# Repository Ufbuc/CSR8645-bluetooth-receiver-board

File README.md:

# CSR8645-bluetooth-receiver-board
Breakout board for F-3188 V2.0 bluetooth board with single ended output signal and onboard power supply.

This is a simple circuit board (43mm x 64mm) to make use of the features of the very common *F-3188 V2.0* which is based on the Qualcomm *CSR8645*. Simply connect power (5V via USB Type B or up to 15V via pin header) and 3.5mm phone connector to get an audio signal in aptX quality.

Pin headers can be used to connect status LEDs and control buttons. Many features can be customized by connecting a supported programmer.
A *MAX97220* board converts the differential ended signal from the *CSR8645* to a single ended signal. The onboard power supply uses a *LD1117 SC-R* to provide a stable input voltage (3.5-3.6V) for both mounted PCBs.

The output level is high enough to drive a dedicated amplifier. If the board is used to directly drive headphones it may be better to skip the onboard power supply and use 5V input voltage as input voltage for the *MAX97220*.

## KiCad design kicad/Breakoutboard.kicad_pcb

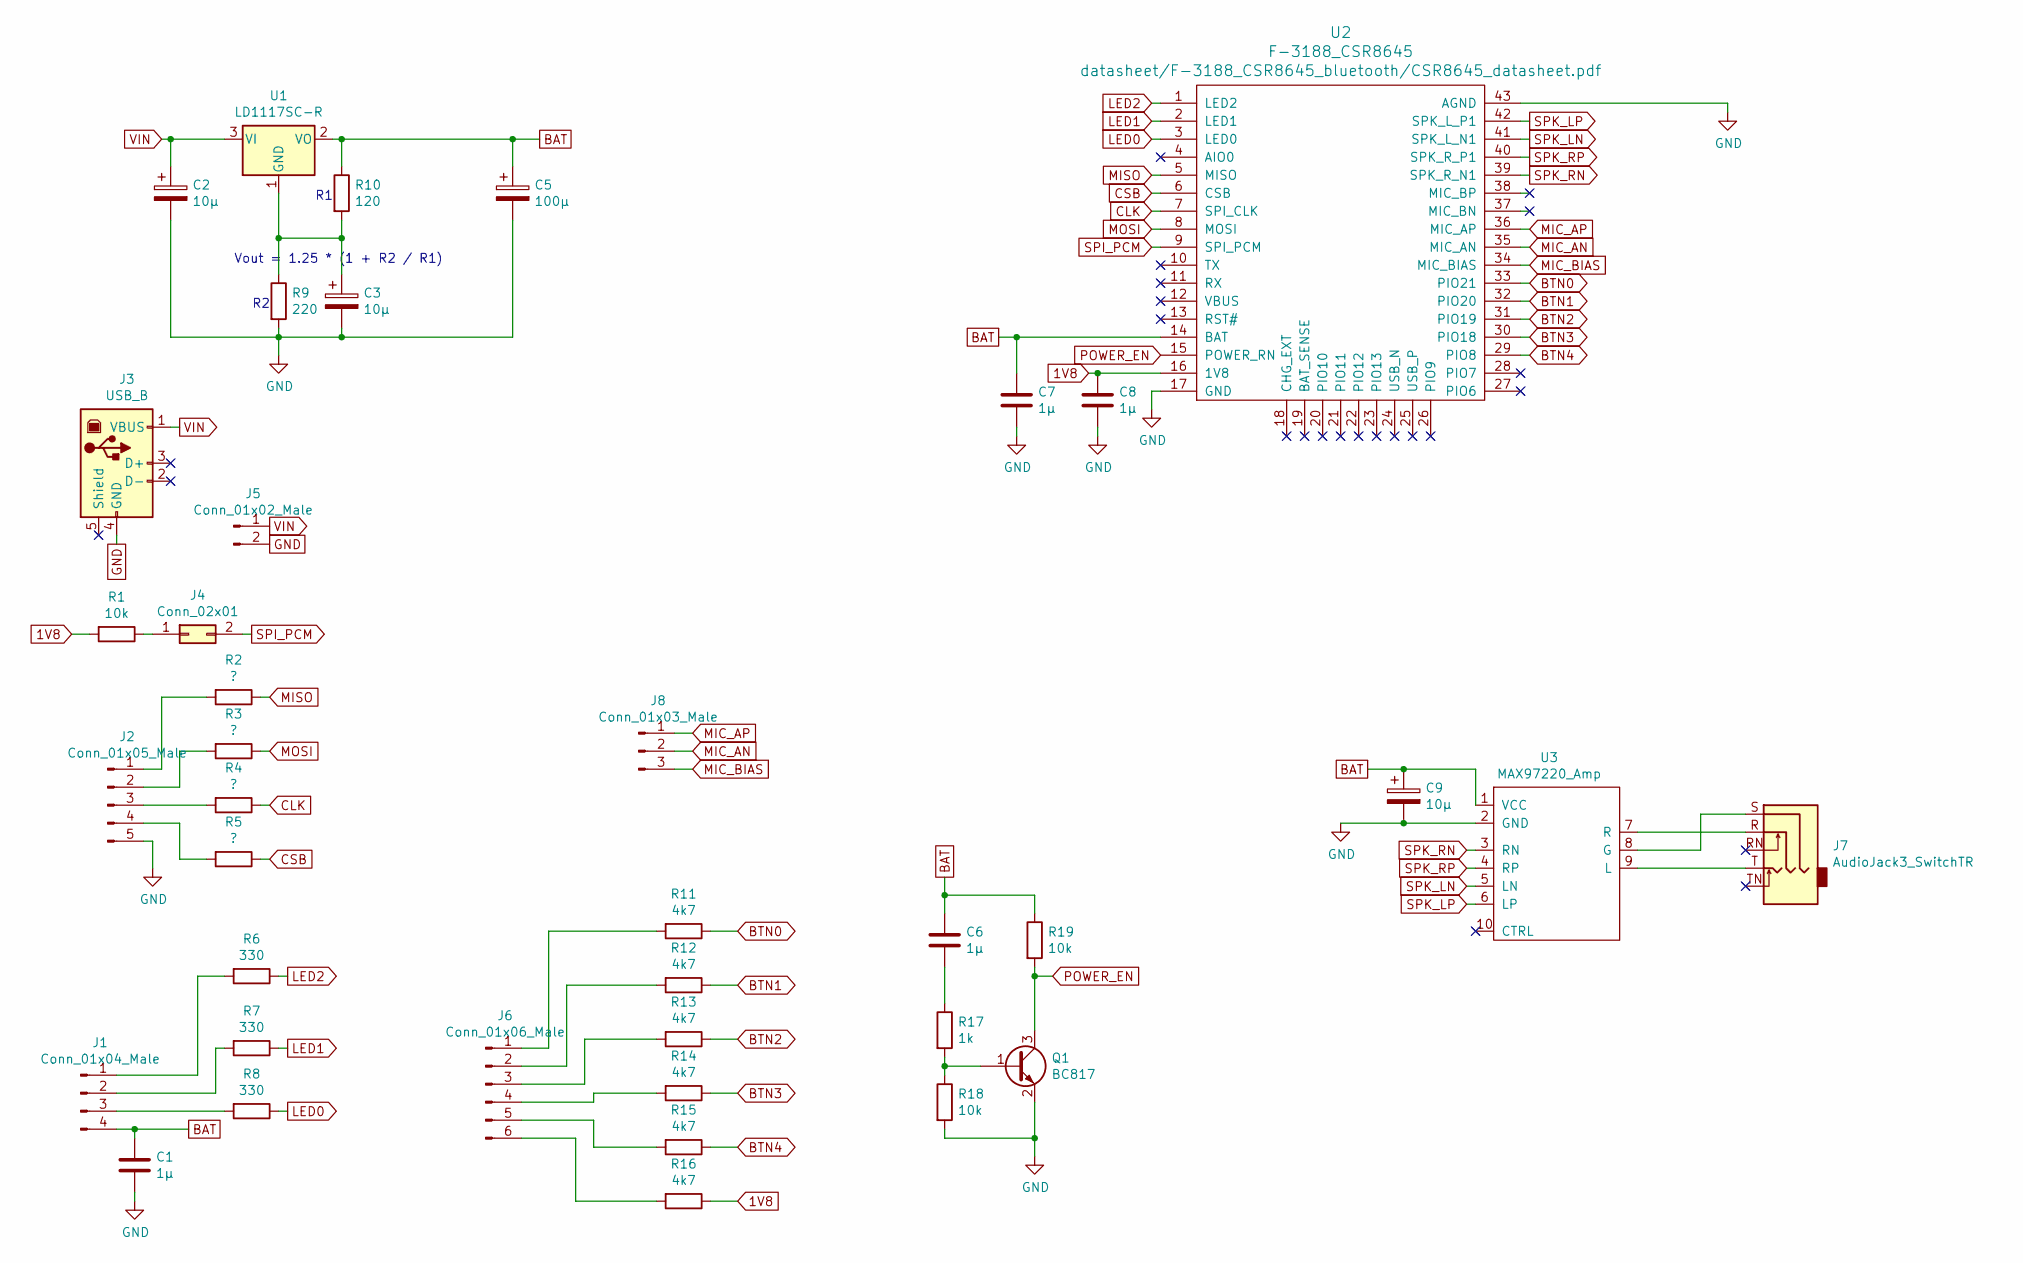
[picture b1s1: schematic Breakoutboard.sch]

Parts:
C1, C6, C7, C8: 1µ; C_0805_2012Metric_Pad1.15x1.40mm_HandSolder
C2, C3, C9: 10µ; CP_Radial_D5.0mm_P2.00mm
C5: 100µ; CP_Radial_D6.3mm_P2.50mm
J1: Conn_01x04_Male; PinHeader_1x04_P2.54mm_Vertical
J2: Conn_01x05_Male; PinHeader_1x05_P2.54mm_Vertical
J3: USB_B; USB_B_OST_USB-B1HSxx_Horizontal
J4: Conn_02x01; PinHeader_2x01_P2.54mm_Vertical
J5: Conn_01x02_Male; PinHeader_1x02_P2.54mm_Vertical
J6: Conn_01x06_Male; PinHeader_1x06_P2.54mm_Vertical
J7: AudioJack3_SwitchTR; Jack_3.5mm_Ledino_KB3SPRS_Horizontal
J8: Conn_01x03_Male; PinHeader_1x03_P2.54mm_Vertical
Q1: BC817; SOT-23
R1, R18, R19: 10k; R_0805_2012Metric_Pad1.15x1.40mm_HandSolder
R2, R3, R4, R5: ?; R_0805_2012Metric_Pad1.15x1.40mm_HandSolder
R6, R7, R8: 330; R_0805_2012Metric_Pad1.15x1.40mm_HandSolder
R9: 220; R_0805_2012Metric_Pad1.15x1.40mm_HandSolder
R10: 120; R_0805_2012Metric_Pad1.15x1.40mm_HandSolder
R11, R12, R13, R14, R15, R16: 4k7; R_0805_2012Metric_Pad1.15x1.40mm_HandSolder
R17: 1k; R_0805_2012Metric_Pad1.15x1.40mm_HandSolder
U1: LD1117SC-R; SOT-223-3_TabPin2
U2: F-3188_CSR8645
U3: MAX97220_Amp; MAX97220_amp

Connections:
1V8: C8.1, R1.2, R16.1, U2.16 (1V8)
BAT: C1.1, C5.1, C6.1, C7.1, C9.1, J1.4, R10.1, R19.1, U1.2 (VO), U2.14 (BAT), U3.1 (VCC)
BTN0: R11.1, U2.33 (PIO21)
BTN1: R12.1, U2.32 (PIO20)
BTN2: R13.1, U2.31 (PIO19)
BTN3: R14.1, U2.30 (PIO18)
BTN4: R15.1, U2.29 (PIO8)
CLK: R4.1, U2.7 (SPI_CLK)
CSB: R5.1, U2.6 (CSB)
GND: C1.2, C2.2, C3.2, C5.2, C7.2, C8.2, C9.2, J2.5, J3.4 (GND), J5.2, Q1.2 (E), R9.2, R18.2, U2.17 (GND), U2.43 (AGND), U3.2 (GND)
LED0: R8.1, U2.3 (LED0)
LED1: R7.1, U2.2 (LED1)
LED2: R6.1, U2.1 (LED2)
MIC_AN: J8.2, U2.35 (MIC_AN)
MIC_AP: J8.1, U2.36 (MIC_AP)
MIC_BIAS: J8.3, U2.34 (MIC_BIAS)
MISO: R2.1, U2.5 (MISO)
MOSI: R3.1, U2.8 (MOSI)
unnamed: C3.1, R9.1, R10.2, U1.1 (GND)
unnamed: C6.2, R17.1
unnamed: J1.1, R6.2
unnamed: J1.2, R7.2
unnamed: J1.3, R8.2
unnamed: J2.1, R2.2
unnamed: J2.2, R3.2
unnamed: J2.3, R4.2
unnamed: J2.4, R5.2
unnamed: J4.1, R1.1
unnamed: J6.1, R11.2
unnamed: J6.2, R12.2
unnamed: J6.3, R13.2
unnamed: J6.4, R14.2
unnamed: J6.5, R15.2
unnamed: J6.6, R16.2
unnamed: J7.R, U3.7 (R)
unnamed: J7.S, U3.8 (G)
unnamed: J7.T, U3.9 (L)
unnamed: Q1.1 (B), R17.2, R18.1
PIO12: U2.22 (PIO12)
PIO13: U2.23 (PIO13)
POWER_EN: Q1.3 (C), R19.2, U2.15 (POWER_RN)
SPI_PCM: J4.2, U2.9 (SPI_PCM)
SPK_LN: U2.41 (SPK_L_N1), U3.5 (LN)
SPK_LP: U2.42 (SPK_L_P1), U3.6 (LP)
SPK_RN: U2.39 (SPK_R_N1), U3.3 (RN)
SPK_RP: U2.40 (SPK_R_P1), U3.4 (RP)
VIN: C2.1, J3.1 (VBUS), J5.1, U1.3 (VI)

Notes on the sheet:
Vout = 1.25 * (1 + R2 / R1)

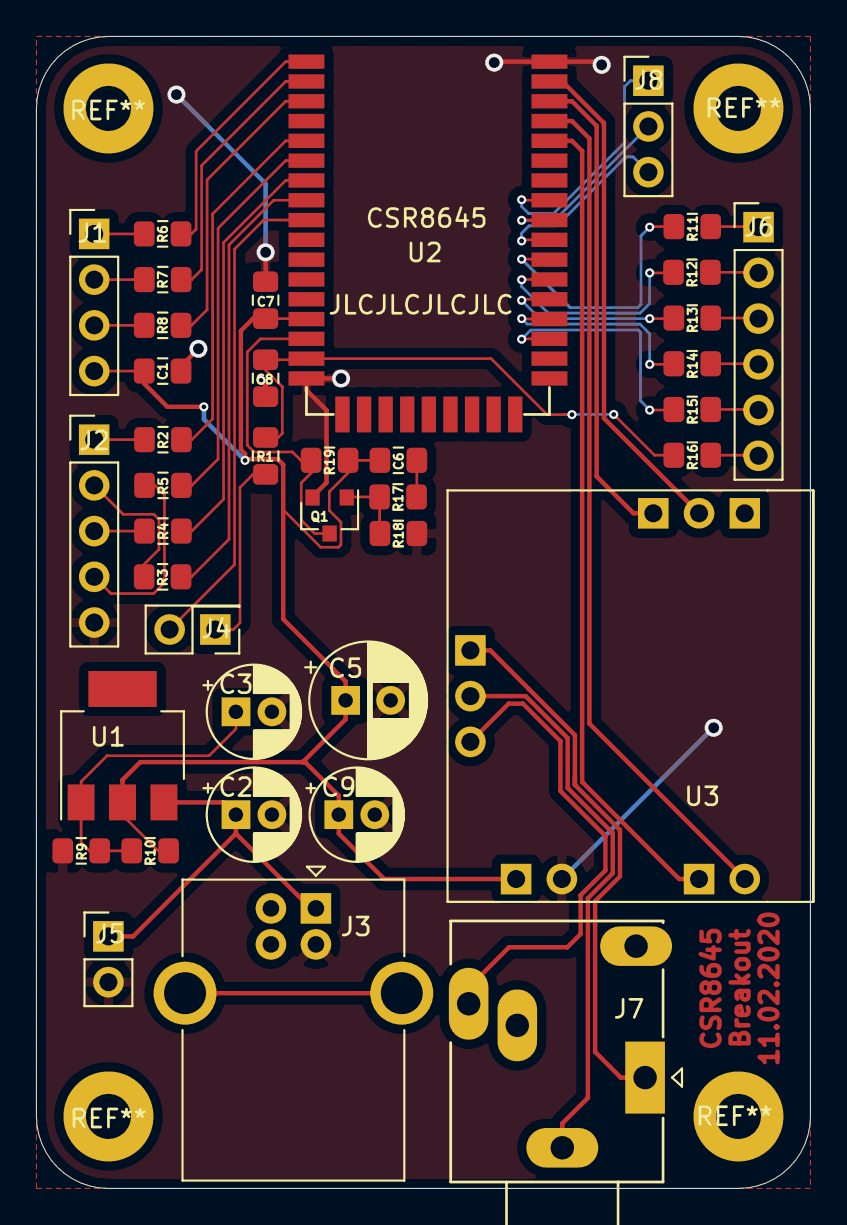
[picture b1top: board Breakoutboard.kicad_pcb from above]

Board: 2 copper layers, 43.0 x 64.0 mm, 39 parts (0 on the bottom side), 45 nets.
